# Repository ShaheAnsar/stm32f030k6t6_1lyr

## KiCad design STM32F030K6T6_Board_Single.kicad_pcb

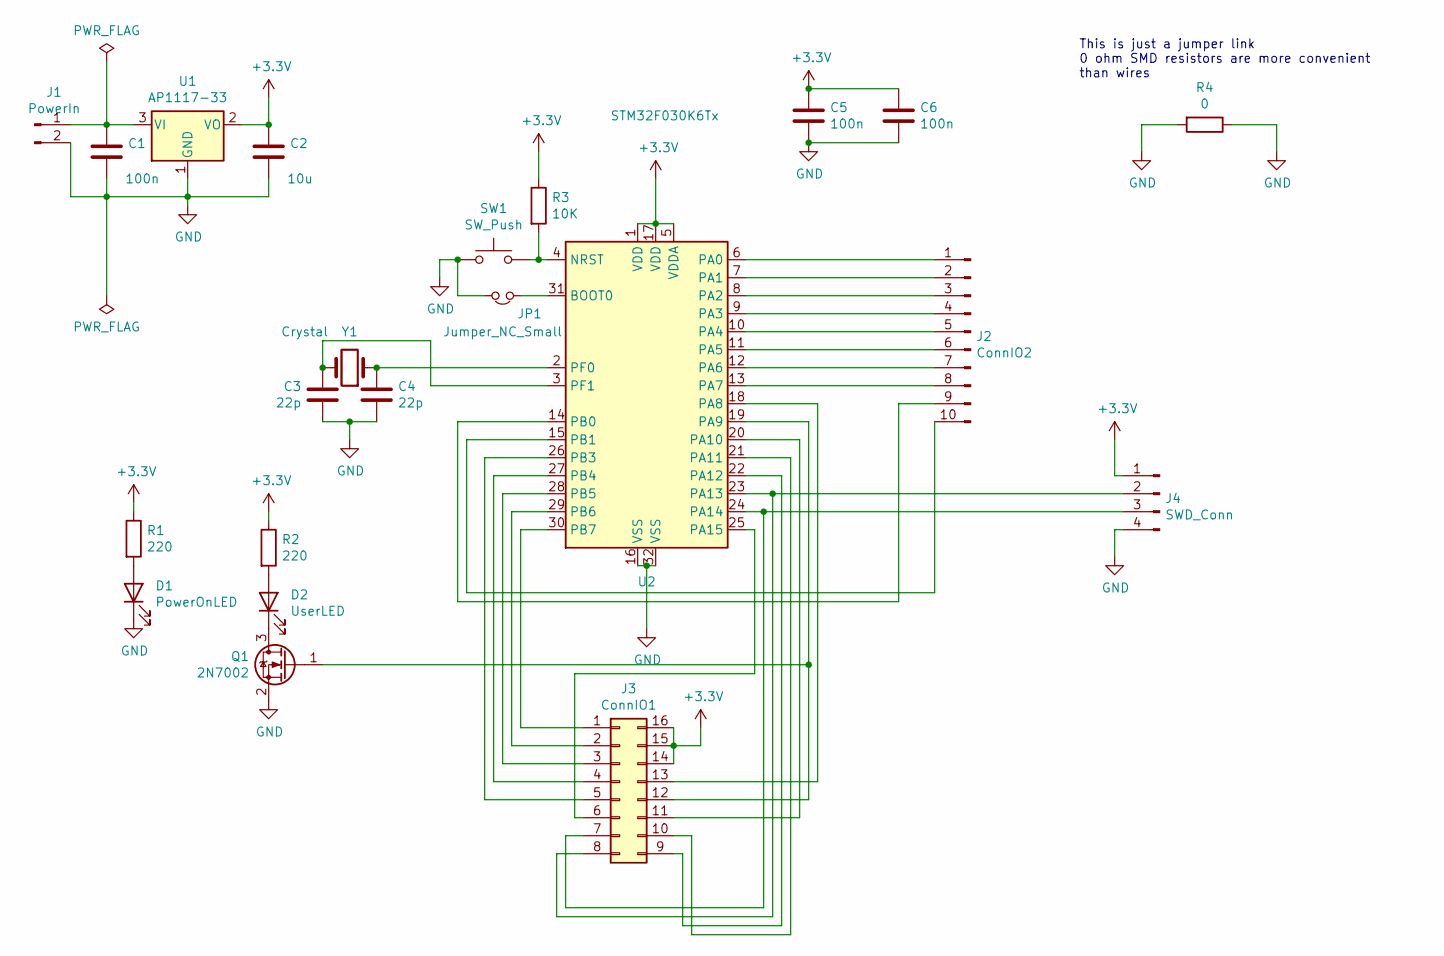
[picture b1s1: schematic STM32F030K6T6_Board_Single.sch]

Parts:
C1, C5, C6: 100n; C_0805_2012Metric_Pad1.18x1.45mm_HandSolder
C2: 10u; C_0805_2012Metric_Pad1.18x1.45mm_HandSolder
C3, C4: 22p; C_0805_2012Metric_Pad1.18x1.45mm_HandSolder
D1: PowerOnLED; LED_0805_2012Metric_Pad1.15x1.40mm_HandSolder
D2: UserLED; LED_0805_2012Metric_Pad1.15x1.40mm_HandSolder
J1: PowerIn; PinHeader_1x02_P2.54mm_Vertical
J2: ConnIO2; PinHeader_1x10_P2.54mm_Vertical
J3: ConnIO1; PinHeader_2x08_P2.54mm_Vertical
J4: SWD_Conn; PinHeader_1x04_P2.54mm_Vertical
JP1: Jumper_NC_Small; SolderJumper-2_P1.3mm_Open_Pad1.0x1.5mm
Q1: 2N7002; SOT-23
R1, R2: 220; R_0805_2012Metric_Pad1.20x1.40mm_HandSolder
R3: 10K; R_0805_2012Metric_Pad1.20x1.40mm_HandSolder
R4: 0; R_1206_3216Metric
SW1: SW_Push; SW_Push_SPST_NO_Alps_SKRK
U1: AP1117-33; SOT-223-3_TabPin2
U2: STM32F030K6Tx; LQFP-32_7x7mm_P0.8mm
Y1: Crystal; Crystal_SMD_HC49-SD

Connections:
+3V3: C2.1, C5.1, C6.1, J3.14, J3.15, J3.16, J4.1, R1.1, R2.1, R3.1, U1.2 (VO), U2.1 (VDD), U2.5 (VDDA), U2.17 (VDD)
GND: C1.2, C2.2, C3.1, C4.1, C5.2, C6.2, D1.1 (K), J1.2, J4.4, JP1.2, Q1.2 (S), R4.1, R4.2, SW1.1, U1.1 (GND), U2.16 (VSS), U2.32 (VSS)
unnamed: C1.1, J1.1, U1.3 (VI)
unnamed: C3.2, U2.3 (PF1), Y1.2
unnamed: C4.2, U2.2 (PF0), Y1.1
unnamed: D1.2 (A), R1.2
unnamed: D2.1 (K), Q1.3 (D)
unnamed: D2.2 (A), R2.2
unnamed: J2.1, U2.6 (PA0)
unnamed: J2.2, U2.7 (PA1)
unnamed: J2.3, U2.8 (PA2)
unnamed: J2.4, U2.9 (PA3)
unnamed: J2.5, U2.10 (PA4)
unnamed: J2.6, U2.11 (PA5)
unnamed: J2.7, U2.12 (PA6)
unnamed: J2.8, U2.13 (PA7)
unnamed: J2.9, U2.14 (PB0)
unnamed: J2.10, U2.15 (PB1)
unnamed: J3.1, U2.30 (PB7)
unnamed: J3.2, U2.29 (PB6)
unnamed: J3.3, U2.28 (PB5)
unnamed: J3.4, U2.27 (PB4)
unnamed: J3.5, U2.26 (PB3)
unnamed: J3.6, U2.25 (PA15)
unnamed: J3.7, J4.3, U2.24 (PA14)
unnamed: J3.8, J4.2, U2.23 (PA13)
unnamed: J3.9, U2.22 (PA12)
unnamed: J3.10, U2.21 (PA11)
unnamed: J3.11, U2.20 (PA10)
unnamed: J3.12, Q1.1 (G), U2.19 (PA9)
unnamed: J3.13, U2.18 (PA8)
unnamed: JP1.1, U2.31 (BOOT0)
unnamed: R3.2, SW1.2, U2.4 (NRST)

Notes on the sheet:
This is just a jumper link 0 ohm SMD resistors are more convenient than wires

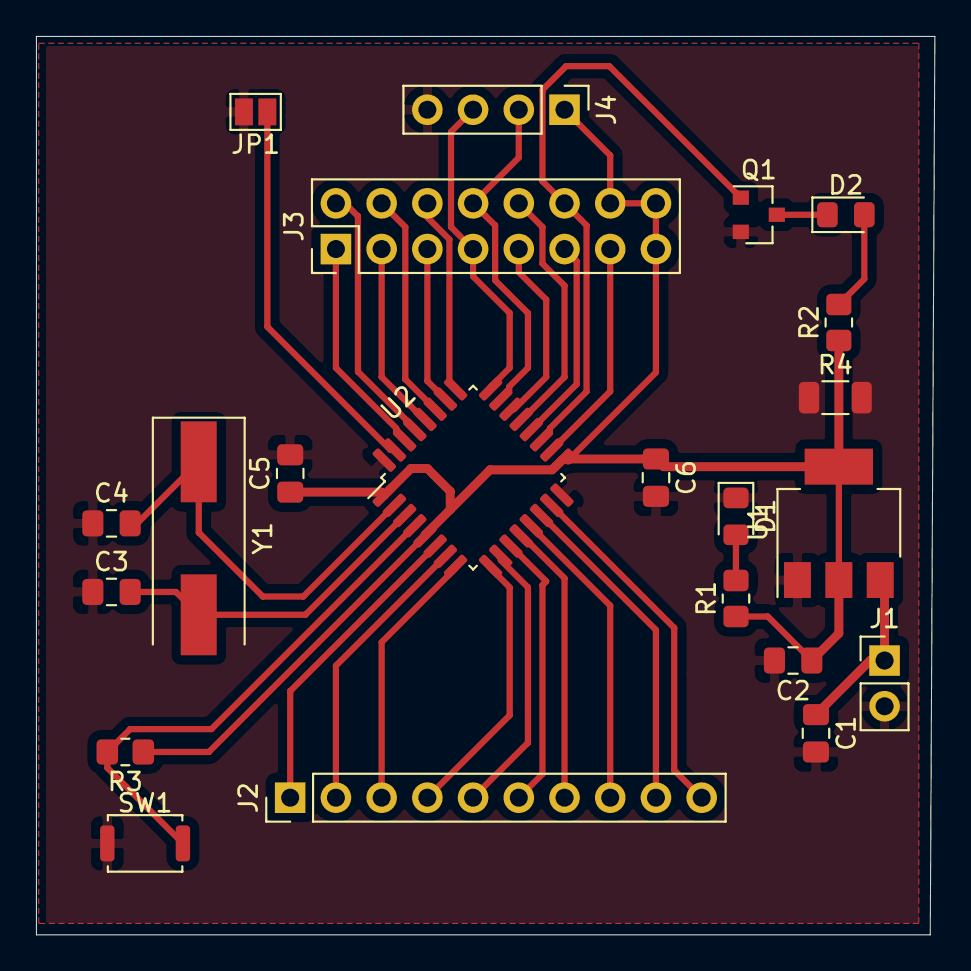
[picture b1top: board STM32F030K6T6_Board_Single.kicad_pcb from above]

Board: 2 copper layers, 49.9 x 49.9 mm, 22 parts (0 on the bottom side), 33 nets.

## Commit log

2021-05-27 PCB finished
2021-05-27 Added a license file
